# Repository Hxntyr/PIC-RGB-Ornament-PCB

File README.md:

# PIC RGB Ornament PCB

A template for making — and a collection of — small RGB LED PCB ornaments.

The core circuit uses a PIC12F1572, CR2450R coin cell, and MCP1640 boost converter to drive 24 low-current RGB LEDs through three shared PWM channels. It is intended to be reused across different board shapes, artwork, and LED layouts without redesigning the electronics each time.

Copy the core project, make your own layout, generate the manufacturing files, and send it off for PCBA — or [purchase the components and assemble it yourself](https://www.digikey.com/en/mylists/list/D7LT6KEKSW).

## What's Included

The [`PIC RGB Ornament Core`](PIC%20RGB%20Ornament%20Core/) folder contains the reusable KiCad project.

Reference files:

* [`PIC RGB Ornament Core_Schematic.pdf`](PIC%20RGB%20Ornament%20Core/PIC%20RGB%20Ornament%20Core_Schematic.pdf) — schematic
* [`PIC RGB Ornament Core_PCB.pdf`](PIC%20RGB%20Ornament%20Core/PIC%20RGB%20Ornament%20Core_PCB.pdf) — component layout with a millimeter scale for quick size reference
* [`PIC RGB Ornament Core.png`](PIC%20RGB%20Ornament%20Core/PIC%20RGB%20Ornament%20Core.png) — 3D viewer reference

Custom footprints are stored in the repository-level [`HX.pretty`](HX.pretty/) library. Each included KiCad project references this library through its local `fp-lib-table`.

The core [`PCBA`](PIC%20RGB%20Ornament%20Core/PCBA/) folder contains files that can generally be reused between designs:

* `BOM.xlsx`
* `FIRMWARE.zip`

The supplied firmware continuously cycles through a slow rainbow at conservative brightness. The PIC is intended to be programmed during assembly, so the finished ornament requires no configuration.

## Making an Ornament

Clone or download the repository and make a copy of the `PIC RGB Ornament Core` project, or use one of the existing ornaments as a starting point.

The electrical design can generally remain unchanged. Modify the board outline, component placement, LED arrangement, artwork, mounting features, and routing as needed for the new design.

If additional custom footprints are required, add them to the root `HX.pretty` library. Projects located one directory below the repository root can use the same `fp-lib-table` entry:

```scheme
(fp_lib_table
  (version 7)
  (lib (name "HX")(type "KiCad")(uri "${KIPRJMOD}/../HX.pretty")(options "")(descr "Project custom footprints"))
)
```

## Preparing a Layout for PCBA

The BOM and firmware can normally be reused as long as the circuit and component selections remain unchanged.

The remaining manufacturing files are layout-specific and should be regenerated for each ornament.

### Gerbers and Drill Files

From KiCad PCB Editor:

`File → Fabrication Outputs → Gerbers`

Export the required copper, solder mask, silkscreen, paste, and `Edge.Cuts` layers, then generate the Excellon drill files.

Zip the Gerber and drill outputs together for fabrication.

### CPL / Pick-and-Place

From KiCad PCB Editor:

`File → Fabrication Outputs → Component Placement`

Export the placement file in millimeters with reference designator, X/Y coordinates, rotation, and board side.

PCBWay refers to this as the **CPL** or centroid file.

### Assembly Drawings

Plot `F.Fab` and `B.Fab` as PDFs with the board outline visible.

These provide a simple component-location and orientation reference for assembly.

### BOM

The baseline BOM is included at:

`PIC RGB Ornament Core/PCBA/BOM.xlsx`

Regenerate or edit it if component values, part numbers, or designators change.

### PIC Firmware

Production firmware is included at:

`PIC RGB Ornament Core/PCBA/FIRMWARE.zip`

For turnkey assembly, program:

`U2 — PIC12F1572T-I/MF`

using the supplied `.hex` file before assembly.

Example production note:

> Program U2 before assembly using the supplied HEX file. After assembly, power the board and verify that all 24 RGB LEDs smoothly cycle through the rainbow.

## Example

[`HappyBirthdayMickey_A`](HappyBirthdayMickey_A/) is an example ornament built from the core design.

Its `PCBA` folder contains a complete set of layout-specific production files:

* Gerber and drill ZIP
* BOM
* CPL / pick-and-place file
* assembly drawing PDFs
* firmware

These are included as a reference for what a completed manufacturing package looks like rather than as production files for the generic core.

## Notes

The default firmware intentionally runs the LEDs fairly dim to reduce coin-cell current and keep the ornament comfortable to view in a dark room.

The CR2450R battery should be installed **after** PCB assembly and should not go through reflow.

## License

This project is released under the **CC0 1.0 Universal Public Domain Dedication**.

Use it, modify it, manufacture it, remix it, or turn it into something completely different.

See [`LICENSE`](LICENSE).

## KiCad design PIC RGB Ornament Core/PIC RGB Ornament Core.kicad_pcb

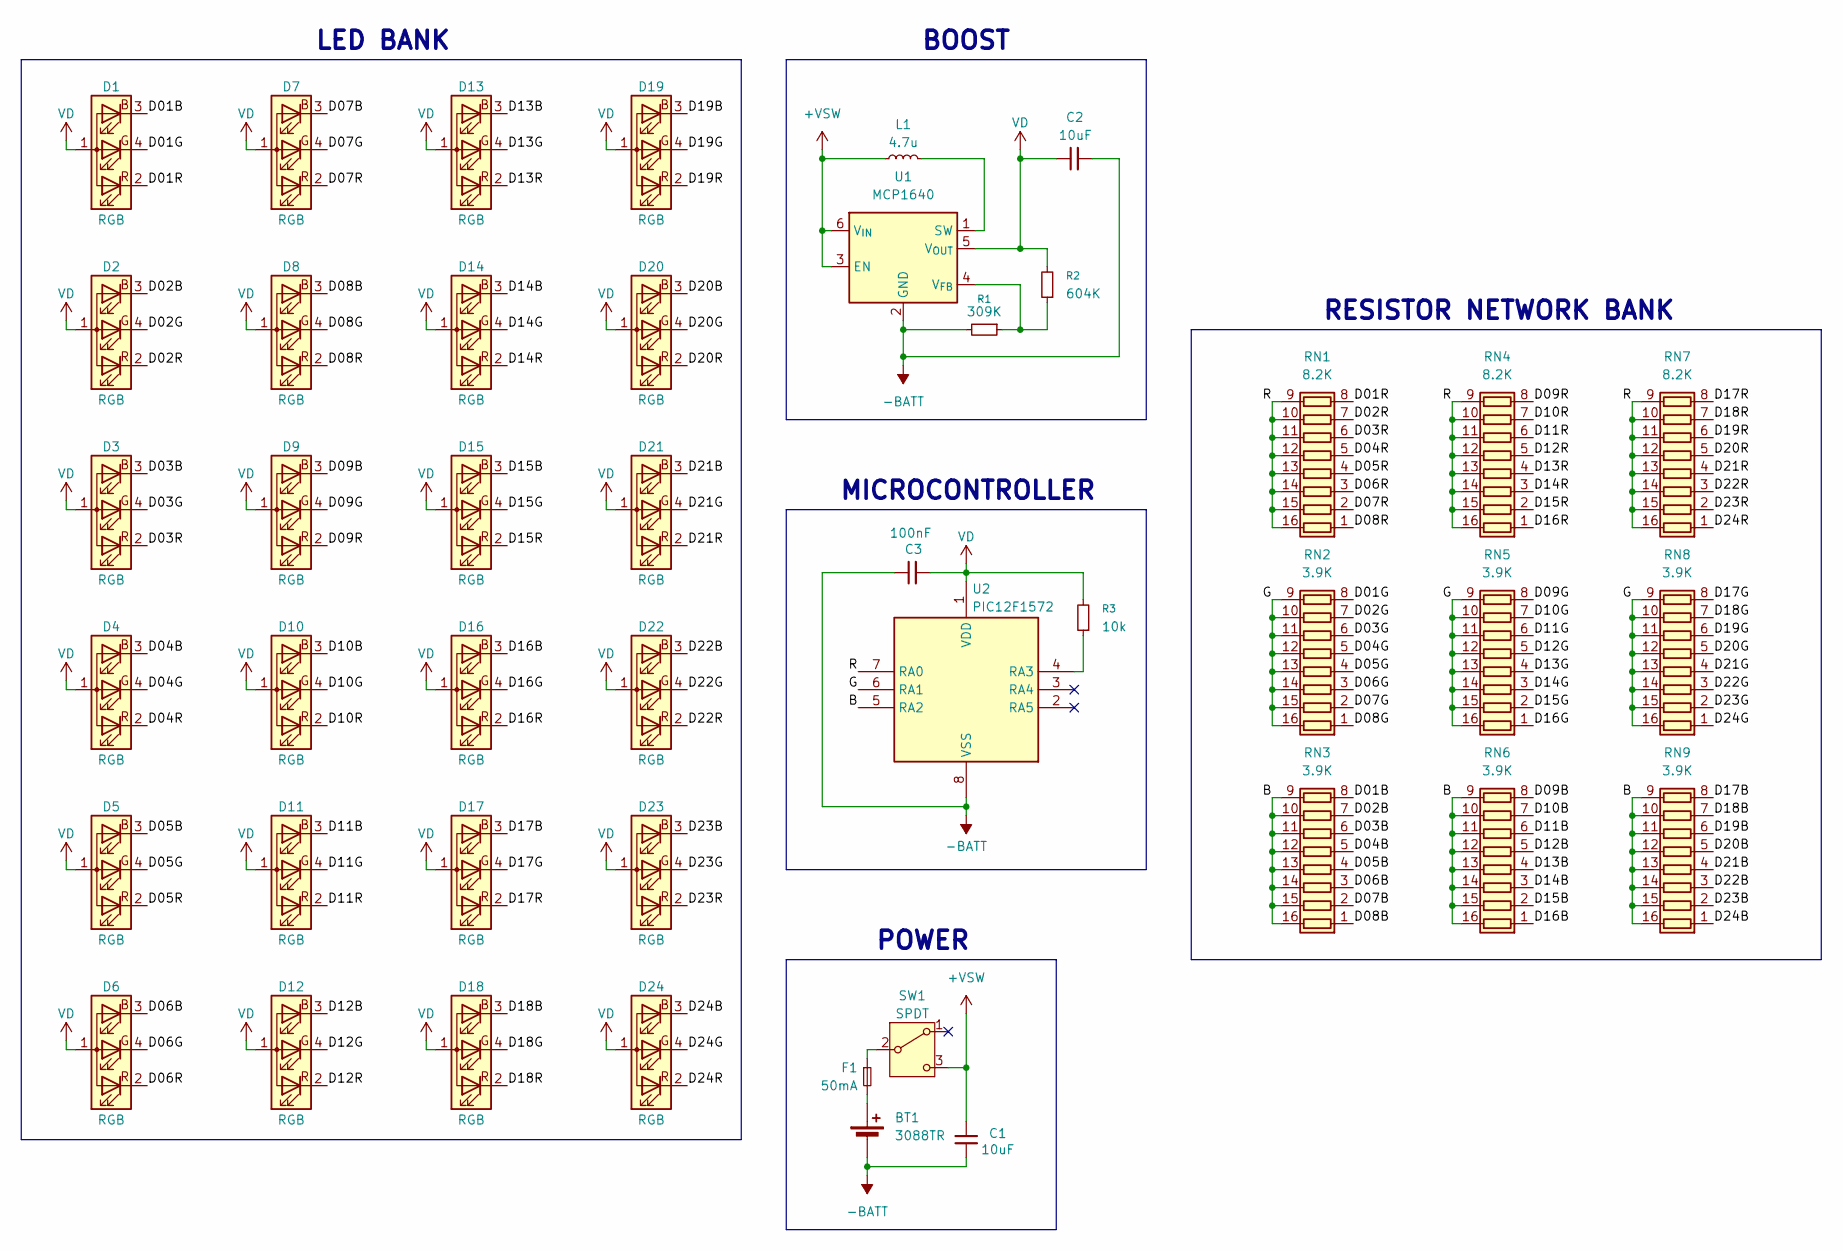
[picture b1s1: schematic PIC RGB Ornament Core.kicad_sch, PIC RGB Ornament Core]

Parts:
BT1: 3088TR; Keystone_3088TR; MPN 3088TR
C1, C2: 10uF; C_0603_1608Metric; MPN GRM188R61A106ME69
C3: 100nF; C_0402_1005Metric; MPN GRM155R71C104KA88J
D1, D2, D3, D4, D5, D6, D7, D8, D9, D10, D11, D12, D13, D14, D15, D16, D17, D18, D19, D20, D21, D22, D23, D24: RGB; Kingbright_APHF1608LSEEQBDZGKC; MPN APHF1608LSEEQBDZGKC
F1: 50mA; Fuse_0603_1608Metric; MPN PTS060315V005
L1: 4.7u; Murata_LQM2MPN4R7MG0L; MPN LQM2MPN4R7MG0L
R1: 309K; R_0402_1005Metric; MPN RC0402FR-07309KL
R2: 604K; R_0402_1005Metric; MPN RC0402FR-07604KL
R3: 10k; R_0402_1005Metric; MPN RC0402FR-0710KL
RN1, RN4, RN7: 8.2K; R_Array_Convex_8x0602; MPN EXB2HV822JV
RN2, RN3, RN5, RN6, RN8, RN9: 3.9K; R_Array_Convex_8x0602; MPN EXB2HV392JV
SW1: SPDT; CK_JS102011JAQN; MPN JS102011JAQN
U1: MCP1640; SOT-23-6; MPN MCP1640T-I/CHY
U2: PIC12F1572; Microchip_PIC12F1572T-IMF; MPN PIC12F1572T-I/MF

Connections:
+VSW: C1.1, L1.2, SW1.3 (C), U1.3 (EN), U1.6 (V_{IN})
-BATT: BT1.2 (-), C1.2, C2.2, C3.2, R1.2, U1.2 (GND), U2.8 (VSS)
/B: RN3.9 (R8.2), RN3.10 (R7.2), RN3.11 (R6.2), RN3.12 (R5.2), RN3.13 (R4.2), RN3.14 (R3.2), RN3.15 (R2.2), RN3.16 (R1.2), RN6.9 (R8.2), RN6.10 (R7.2), RN6.11 (R6.2), RN6.12 (R5.2), RN6.13 (R4.2), RN6.14 (R3.2), RN6.15 (R2.2), RN6.16 (R1.2), RN9.9 (R8.2), RN9.10 (R7.2), RN9.11 (R6.2), RN9.12 (R5.2), RN9.13 (R4.2), RN9.14 (R3.2), RN9.15 (R2.2), RN9.16 (R1.2), U2.5 (RA2)
/D01B: D1.3 (BK), RN3.8 (R8.1)
/D01G: D1.4 (GK), RN2.8 (R8.1)
/D01R: D1.2 (RK), RN1.8 (R8.1)
/D02B: D2.3 (BK), RN3.7 (R7.1)
/D02G: D2.4 (GK), RN2.7 (R7.1)
/D02R: D2.2 (RK), RN1.7 (R7.1)
/D03B: D3.3 (BK), RN3.6 (R6.1)
/D03G: D3.4 (GK), RN2.6 (R6.1)
/D03R: D3.2 (RK), RN1.6 (R6.1)
/D04B: D4.3 (BK), RN3.5 (R5.1)
/D04G: D4.4 (GK), RN2.5 (R5.1)
/D04R: D4.2 (RK), RN1.5 (R5.1)
/D05B: D5.3 (BK), RN3.4 (R4.1)
/D05G: D5.4 (GK), RN2.4 (R4.1)
/D05R: D5.2 (RK), RN1.4 (R4.1)
/D06B: D6.3 (BK), RN3.3 (R3.1)
/D06G: D6.4 (GK), RN2.3 (R3.1)
/D06R: D6.2 (RK), RN1.3 (R3.1)
/D07B: D7.3 (BK), RN3.2 (R2.1)
/D07G: D7.4 (GK), RN2.2 (R2.1)
/D07R: D7.2 (RK), RN1.2 (R2.1)
/D08B: D8.3 (BK), RN3.1 (R1.1)
/D08G: D8.4 (GK), RN2.1 (R1.1)
/D08R: D8.2 (RK), RN1.1 (R1.1)
/D09B: D9.3 (BK), RN6.8 (R8.1)
/D09G: D9.4 (GK), RN5.8 (R8.1)
/D09R: D9.2 (RK), RN4.8 (R8.1)
/D10B: D10.3 (BK), RN6.7 (R7.1)
/D10G: D10.4 (GK), RN5.7 (R7.1)
/D10R: D10.2 (RK), RN4.7 (R7.1)
/D11B: D11.3 (BK), RN6.6 (R6.1)
/D11G: D11.4 (GK), RN5.6 (R6.1)
/D11R: D11.2 (RK), RN4.6 (R6.1)
/D12B: D12.3 (BK), RN6.5 (R5.1)
/D12G: D12.4 (GK), RN5.5 (R5.1)
/D12R: D12.2 (RK), RN4.5 (R5.1)
/D13B: D13.3 (BK), RN6.4 (R4.1)
/D13G: D13.4 (GK), RN5.4 (R4.1)
/D13R: D13.2 (RK), RN4.4 (R4.1)
/D14B: D14.3 (BK), RN6.3 (R3.1)
/D14G: D14.4 (GK), RN5.3 (R3.1)
/D14R: D14.2 (RK), RN4.3 (R3.1)
/D15B: D15.3 (BK), RN6.2 (R2.1)
/D15G: D15.4 (GK), RN5.2 (R2.1)
/D15R: D15.2 (RK), RN4.2 (R2.1)
/D16B: D16.3 (BK), RN6.1 (R1.1)
/D16G: D16.4 (GK), RN5.1 (R1.1)
/D16R: D16.2 (RK), RN4.1 (R1.1)
/D17B: D17.3 (BK), RN9.8 (R8.1)
/D17G: D17.4 (GK), RN8.8 (R8.1)
/D17R: D17.2 (RK), RN7.8 (R8.1)
/D18B: D18.3 (BK), RN9.7 (R7.1)
/D18G: D18.4 (GK), RN8.7 (R7.1)
/D18R: D18.2 (RK), RN7.7 (R7.1)
/D19B: D19.3 (BK), RN9.6 (R6.1)
/D19G: D19.4 (GK), RN8.6 (R6.1)
/D19R: D19.2 (RK), RN7.6 (R6.1)
/D20B: D20.3 (BK), RN9.5 (R5.1)
/D20G: D20.4 (GK), RN8.5 (R5.1)
/D20R: D20.2 (RK), RN7.5 (R5.1)
/D21B: D21.3 (BK), RN9.4 (R4.1)
/D21G: D21.4 (GK), RN8.4 (R4.1)
/D21R: D21.2 (RK), RN7.4 (R4.1)
/D22B: D22.3 (BK), RN9.3 (R3.1)
/D22G: D22.4 (GK), RN8.3 (R3.1)
/D22R: D22.2 (RK), RN7.3 (R3.1)
/D23B: D23.3 (BK), RN9.2 (R2.1)
/D23G: D23.4 (GK), RN8.2 (R2.1)
/D23R: D23.2 (RK), RN7.2 (R2.1)
/D24B: D24.3 (BK), RN9.1 (R1.1)
/D24G: D24.4 (GK), RN8.1 (R1.1)
/D24R: D24.2 (RK), RN7.1 (R1.1)
/G: RN2.9 (R8.2), RN2.10 (R7.2), RN2.11 (R6.2), RN2.12 (R5.2), RN2.13 (R4.2), RN2.14 (R3.2), RN2.15 (R2.2), RN2.16 (R1.2), RN5.9 (R8.2), RN5.10 (R7.2), RN5.11 (R6.2), RN5.12 (R5.2), RN5.13 (R4.2), RN5.14 (R3.2), RN5.15 (R2.2), RN5.16 (R1.2), RN8.9 (R8.2), RN8.10 (R7.2), RN8.11 (R6.2), RN8.12 (R5.2), RN8.13 (R4.2), RN8.14 (R3.2), RN8.15 (R2.2), RN8.16 (R1.2), U2.6 (RA1)
/R: RN1.9 (R8.2), RN1.10 (R7.2), RN1.11 (R6.2), RN1.12 (R5.2), RN1.13 (R4.2), RN1.14 (R3.2), RN1.15 (R2.2), RN1.16 (R1.2), RN4.9 (R8.2), RN4.10 (R7.2), RN4.11 (R6.2), RN4.12 (R5.2), RN4.13 (R4.2), RN4.14 (R3.2), RN4.15 (R2.2), RN4.16 (R1.2), RN7.9 (R8.2), RN7.10 (R7.2), RN7.11 (R6.2), RN7.12 (R5.2), RN7.13 (R4.2), RN7.14 (R3.2), RN7.15 (R2.2), RN7.16 (R1.2), U2.7 (RA0)
unnamed: BT1.1 (+), F1.2
unnamed: F1.1, SW1.2 (B)
unnamed: L1.1, U1.1 (SW)
unnamed: R1.1, R2.1, U1.4 (V_{FB})
unnamed: R3.1, U2.4 (RA3)
VD: C2.1, C3.1, D1.1 (A), D2.1 (A), D3.1 (A), D4.1 (A), D5.1 (A), D6.1 (A), D7.1 (A), D8.1 (A), D9.1 (A), D10.1 (A), D11.1 (A), D12.1 (A), D13.1 (A), D14.1 (A), D15.1 (A), D16.1 (A), D17.1 (A), D18.1 (A), D19.1 (A), D20.1 (A), D21.1 (A), D22.1 (A), D23.1 (A), D24.1 (A), R2.2, R3.2, U1.5 (V_{OUT}), U2.1 (VDD)

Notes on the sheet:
RESISTOR NETWORK BANK
BOOST
POWER
LED BANK
MICROCONTROLLER

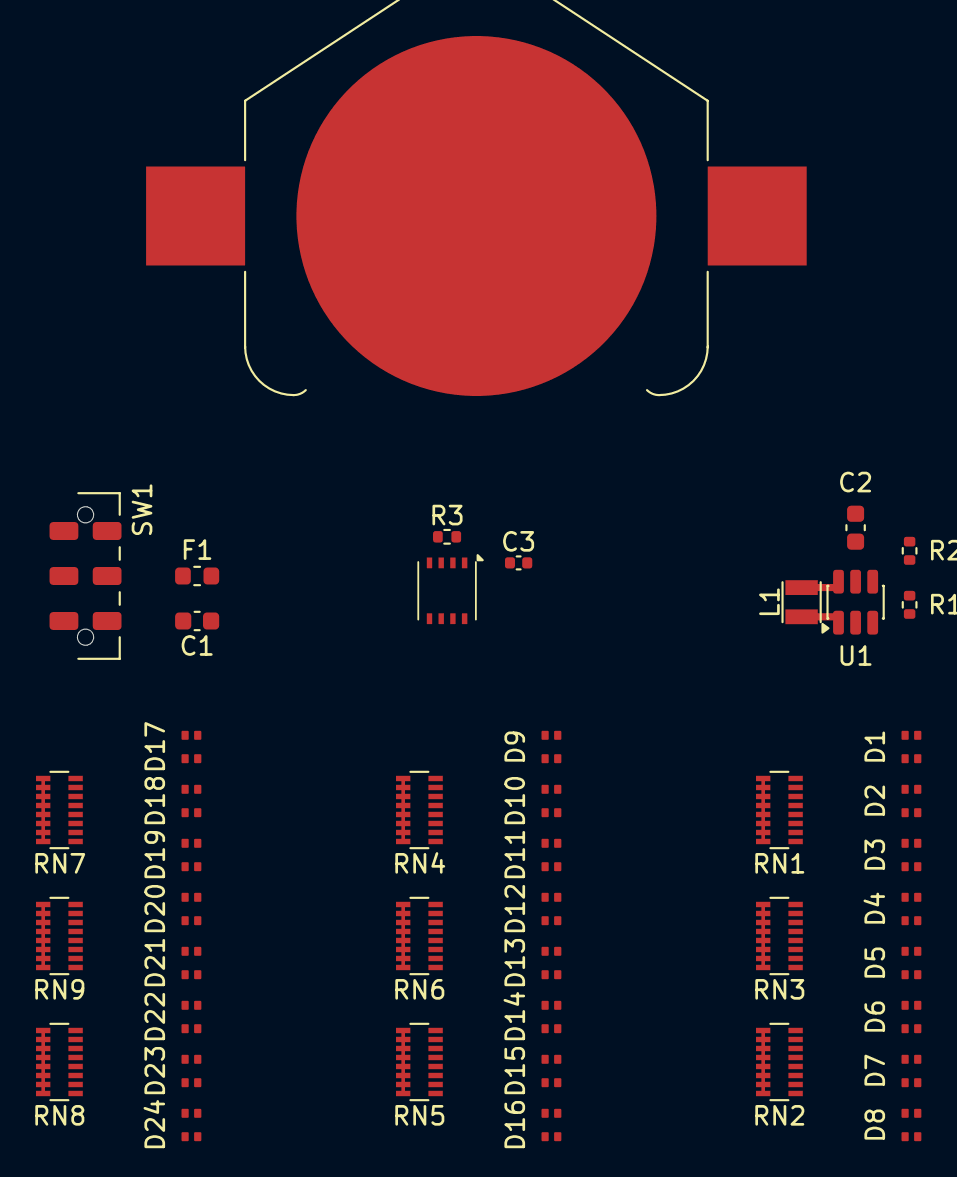
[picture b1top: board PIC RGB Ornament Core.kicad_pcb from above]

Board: 2 copper layers, 45 parts (0 on the bottom side), 83 nets.
